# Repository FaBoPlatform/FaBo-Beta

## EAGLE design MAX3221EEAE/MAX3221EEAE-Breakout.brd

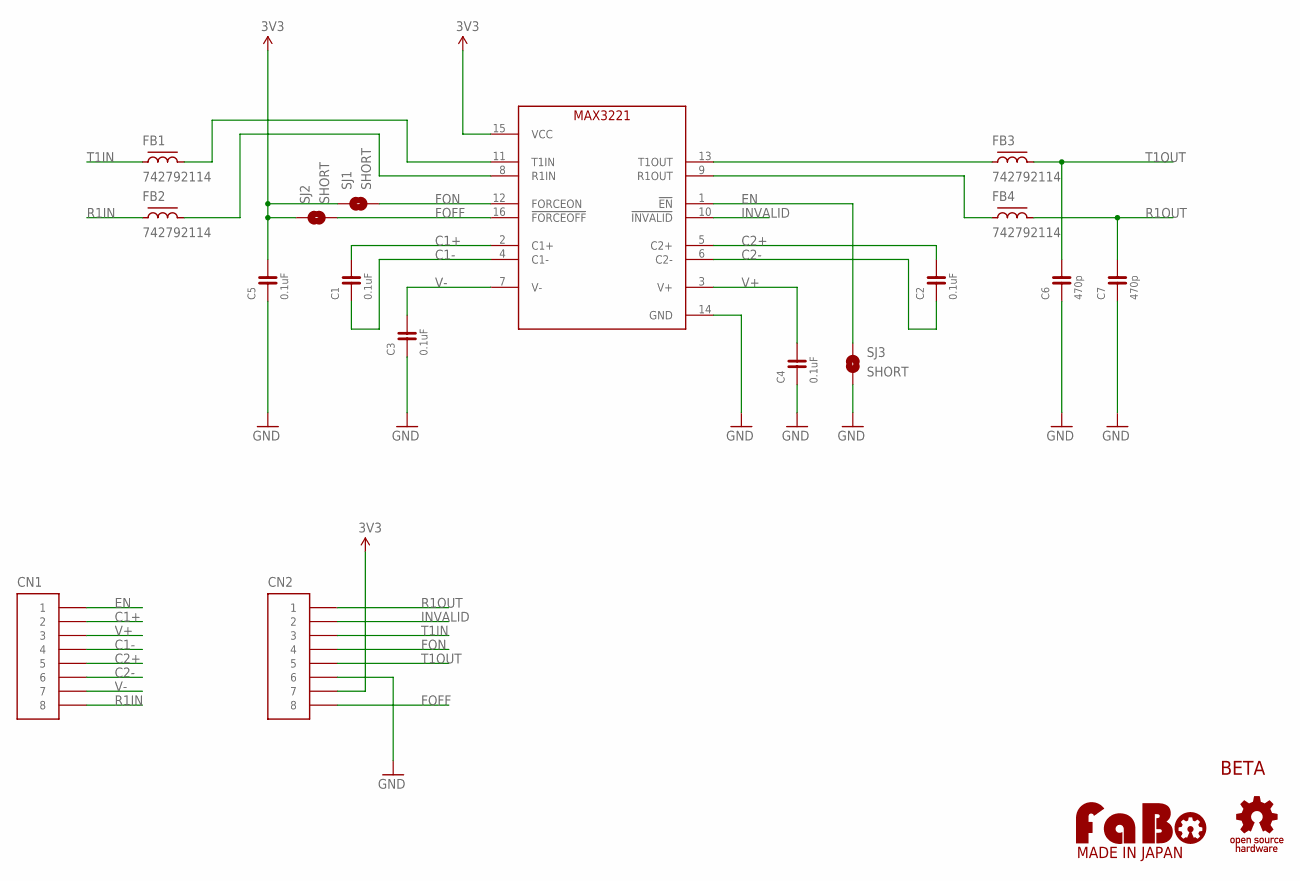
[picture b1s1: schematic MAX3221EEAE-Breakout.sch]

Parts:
C1, C2, C3, C4, C5: 0.1uF; 0603
C6, C7: 470p; 0603
CN1, CN2: PIN_HEADER_1X8; PIN_1X8
FB1, FB2, FB3, FB4: 742792114; EIA1206
IC1: MAX3221EEAE; SSOP-16
SJ1, SJ2, SJ3: SHORT; SMD-JUMPER-2-SHORT
U$2: LOGO_FABO-M_BOTTOM; LOGO_FABO_MS_BOTTOM
U$3: LOGO_OSHW-M_BOTTOM; LOGO_OSHW_M_BOTTOM

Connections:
3V3: C5.2, CN2.7, IC1.15 (VCC), SJ1.1, SJ2.1
C1+: C1.2, CN1.2, IC1.2 (C1+)
C1-: C1.1, CN1.4, IC1.4 (C1-)
C2+: C2.2, CN1.5, IC1.5 (C2+)
C2-: C2.1, CN1.6, IC1.6 (C2-)
EN: CN1.1, IC1.1 (!EN), SJ3.1
FOFF: CN2.8, IC1.16 (!FORCEOFF), SJ2.2
FON: CN2.4, IC1.12 (FORCEON), SJ1.2
GND: C3.1, C4.1, C5.1, C6.1, C7.1, CN2.6, IC1.14 (GND), SJ3.2
INVALID: CN2.2, IC1.10 (!INVALID)
R1IN: CN1.8, FB2.1
R1IN_R: FB2.2, IC1.8 (R1IN)
R1OUT: C7.2, CN2.1, FB4.2
R1OUT_R: FB4.1, IC1.9 (R1OUT)
T1IN: CN2.3, FB1.1
T1IN_R: FB1.2, IC1.11 (T1IN)
T1OUT: C6.2, CN2.5, FB3.2
T1OUT_R: FB3.1, IC1.13 (T1OUT)
V+: C4.2, CN1.3, IC1.3 (V+)
V-: C3.2, CN1.7, IC1.7 (V-)

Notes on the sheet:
BETA

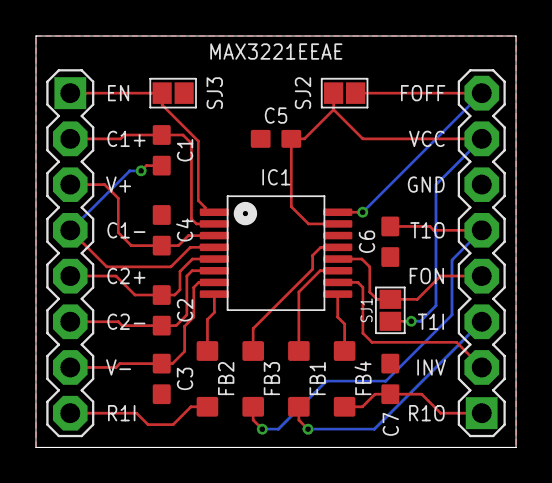
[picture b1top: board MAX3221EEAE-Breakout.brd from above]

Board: 2 copper layers, 26.7 x 22.9 mm, 19 parts (0 on the bottom side), 20 nets.

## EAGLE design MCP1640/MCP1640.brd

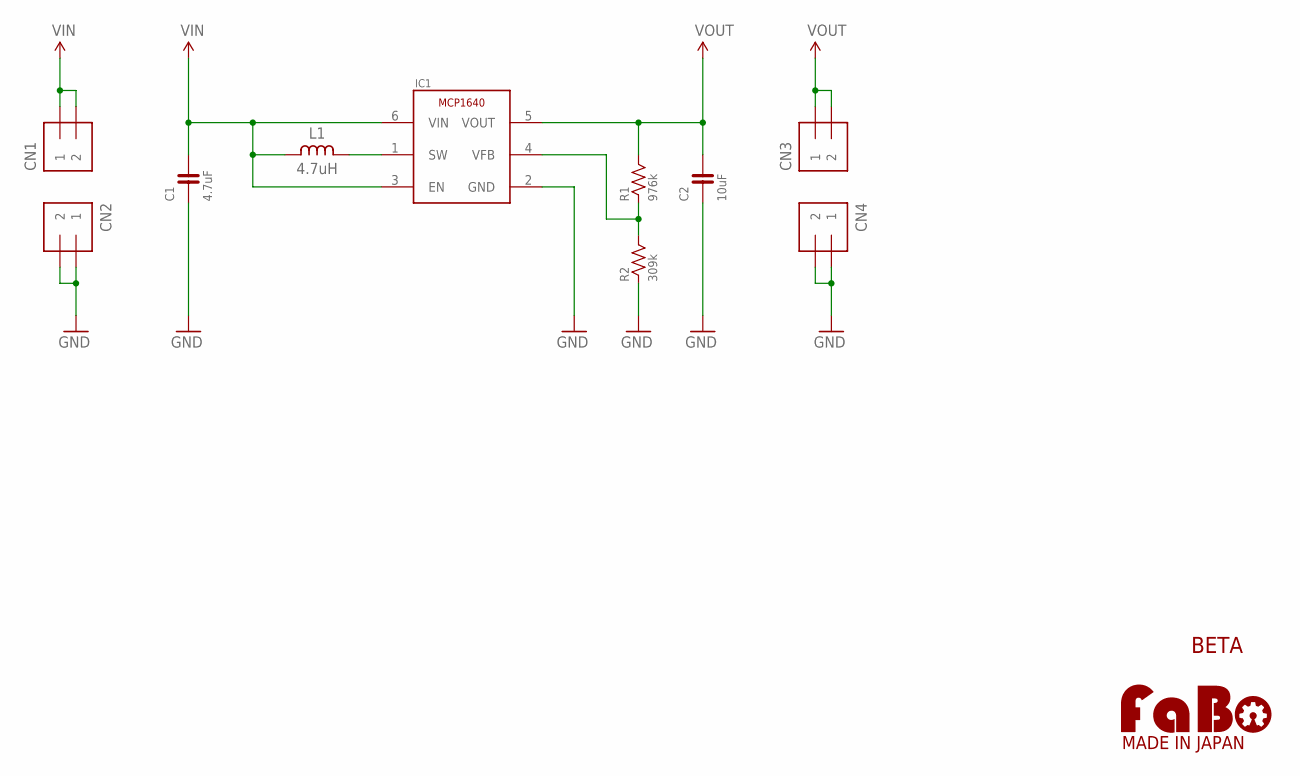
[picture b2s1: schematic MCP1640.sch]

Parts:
C1: 4.7uF; 0603-NARROW
C2: 10uF; 0603-NARROW
CN1, CN2, CN3, CN4: PIN_HEADER_1X2; PIN_1X2
IC1: MCP1640T; SOT-23-6
L1: 4.7uH; LQH3NPN
R1: 976k; 0603-NARROW
R2: 309k; 0603-NARROW
U$2: LOGO_FABO-M_BOTTOM; LOGO_FABO_MS_BOTTOM

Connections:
GND: C1.1, C2.1, CN2.1, CN2.2, CN4.1, CN4.2, IC1.2 (GND), R2.1
unnamed: IC1.1 (SW), L1.2
unnamed: IC1.4 (VFB), R1.1, R2.2
VIN: C1.2, CN1.1, CN1.2, IC1.3 (EN), IC1.6 (VIN), L1.1
VOUT: C2.2, CN3.1, CN3.2, IC1.5 (VOUT), R1.2

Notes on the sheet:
BETA

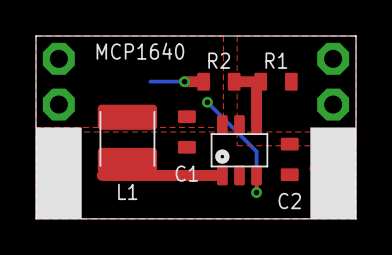
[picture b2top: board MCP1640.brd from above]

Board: 2 copper layers, 17.8 x 10.2 mm, 11 parts (0 on the bottom side), 5 nets.

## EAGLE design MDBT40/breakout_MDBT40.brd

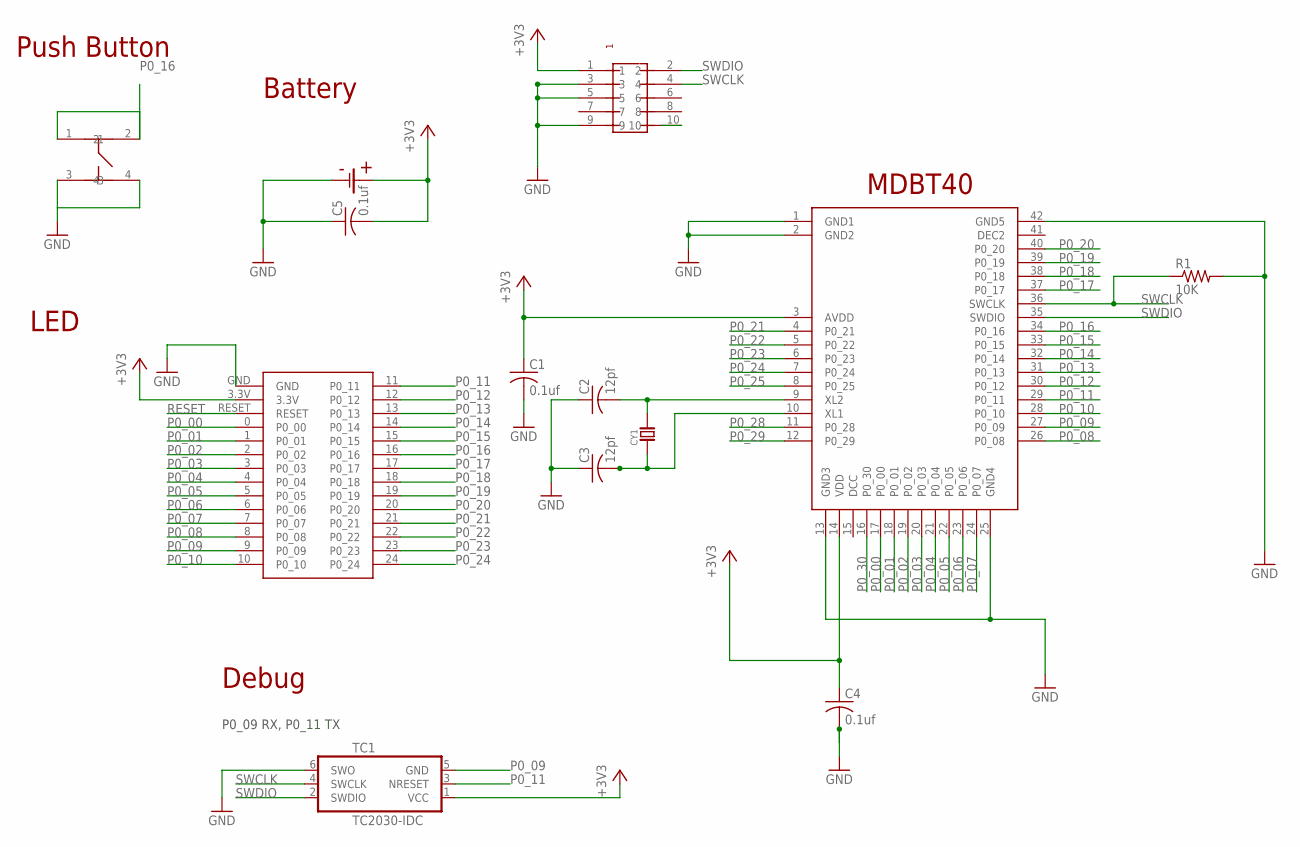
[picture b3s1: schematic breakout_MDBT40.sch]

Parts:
C1, C4, C5: 0.1uf; C0603
C2, C3: 12pf; C0603
CY1: CRYSTALABS07; ABRACOM-ABS07-32.768KHZ
R1: 10K; R0603
TC1: TC2030-IDC
U$1: RAYTAC-MDBT40
U$3: BLE-BREAKOUT-NORDIC
U$4: PIN-HEADER-SMT(1.27MM)2X5
U$5: SWICTH-4P(KMR2); SWITCH-4P(KMR2)
U$8: SMTU-TOP2032; SMTU-2032

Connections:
+3V3: C1.1, C4.1, C5.2, TC1.1 (VCC), U$1.3 (AVDD), U$1.14 (VDD), U$3.3.3V, U$4.1, U$8.+
GND: C1.2, C2.1, C3.1, C4.2, C5.1, R1.2, TC1.6 (SWO), U$1.1 (GND1), U$1.2 (GND2), U$1.13 (GND3), U$1.25 (GND4), U$1.42 (GND5), U$3.GND, U$4.3, U$4.5, U$4.9, U$5.3, U$5.4, U$8.-
unnamed: C2.2, CY1.P$2, U$1.9 (XL2)
unnamed: C3.2, CY1.P$1, U$1.10 (XL1)
P0_00: U$1.17 (P0_00), U$3.0 (P0_00)
P0_01: U$1.18 (P0_01), U$3.1 (P0_01)
P0_02: U$1.19 (P0_02), U$3.2 (P0_02)
P0_03: U$1.20 (P0_03), U$3.3 (P0_03)
P0_04: U$1.21 (P0_04), U$3.4 (P0_04)
P0_05: U$1.22 (P0_05), U$3.5 (P0_05)
P0_06: U$1.23 (P0_06), U$3.6 (P0_06)
P0_07: U$1.24 (P0_07), U$3.7 (P0_07)
P0_08: U$1.26 (P0_08), U$3.8 (P0_08)
P0_09: TC1.5 (GND), U$1.27 (P0_09), U$3.9 (P0_09)
P0_10: U$1.28 (P0_10), U$3.10 (P0_10)
P0_11: TC1.3 (NRESET), U$1.29 (P0_11), U$3.11 (P0_11)
P0_12: U$1.30 (P0_12), U$3.12 (P0_12)
P0_13: U$1.31 (P0_13), U$3.13 (P0_13)
P0_14: U$1.32 (P0_14), U$3.14 (P0_14)
P0_15: U$1.33 (P0_15), U$3.15 (P0_15)
P0_16: U$1.34 (P0_16), U$3.16 (P0_16), U$5.1, U$5.2
P0_17: U$1.37 (P0_17), U$3.17 (P0_17)
P0_18: U$1.38 (P0_18), U$3.18 (P0_18)
P0_19: U$1.39 (P0_19), U$3.19 (P0_19)
P0_20: U$1.40 (P0_20), U$3.20 (P0_20)
P0_21: U$1.4 (P0_21), U$3.21 (P0_21)
P0_22: U$1.5 (P0_22), U$3.22 (P0_22)
P0_23: U$1.6 (P0_23), U$3.23 (P0_23)
P0_24: U$1.7 (P0_24), U$3.24 (P0_24)
P0_25: U$1.8 (P0_25)
P0_28: U$1.11 (P0_28)
P0_29: U$1.12 (P0_29)
P0_30: U$1.16 (P0_30)
RESET: U$3.RESET
RESET1: U$4.10
SWCLK: R1.1, TC1.4 (SWCLK), U$1.36 (SWCLK), U$4.4
SWDIO: TC1.2 (SWDIO), U$1.35 (SWDIO), U$4.2

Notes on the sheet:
Battery
Push Button
MDBT40
LED
Debug
P0_09 RX, P0_11 TX

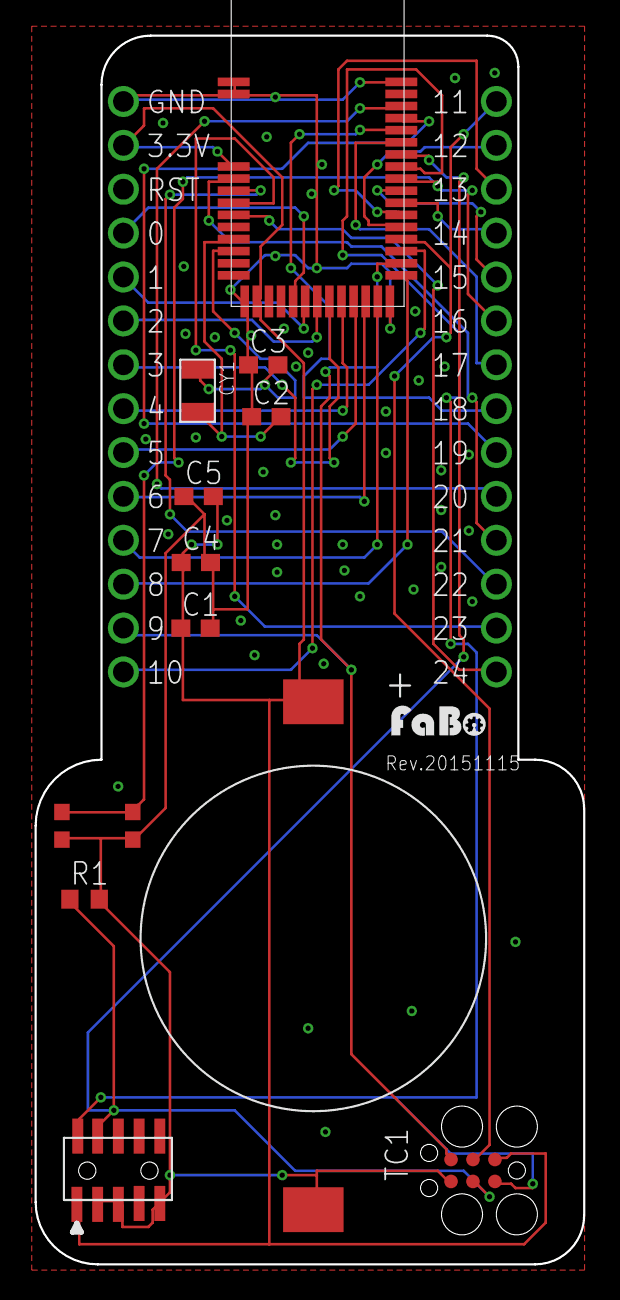
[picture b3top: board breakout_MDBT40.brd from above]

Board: 2 copper layers, 31.8 x 71.1 mm, 14 parts (0 on the bottom side), 31 nets.

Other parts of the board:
U$7: LOGO_FABO_S

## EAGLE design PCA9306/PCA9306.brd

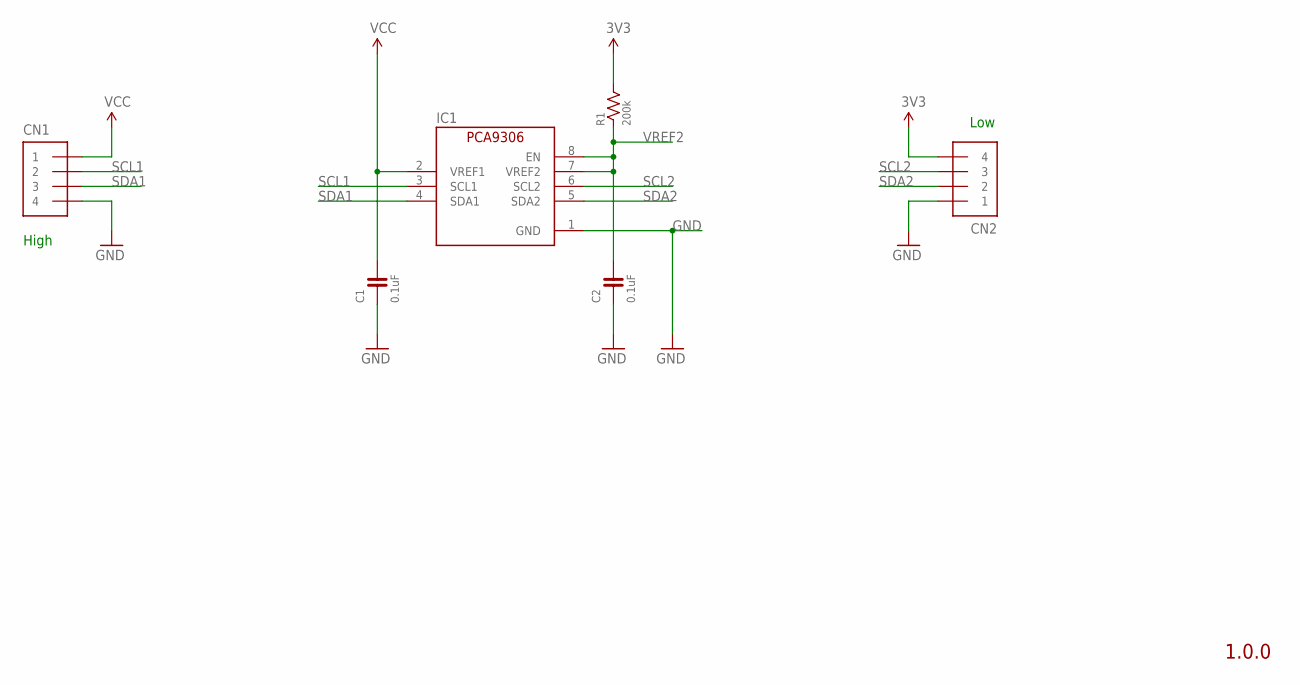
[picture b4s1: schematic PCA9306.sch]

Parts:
C1, C2: 0.1uF; 0603
CN1, CN2: PIN_HEADER_1X4; PIN_1X4_SNEAKY
IC1: TI-PCA9306DQE; TI-PCA9306
R1: 200k; 0603

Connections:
3V3: CN2.4, R1.2
GND: C1.1, C2.1, CN1.4, CN2.1, IC1.1 (GND)
SCL1: CN1.2, IC1.3 (SCL1)
SCL2: CN2.3, IC1.6 (SCL2)
SDA1: CN1.3, IC1.4 (SDA1)
SDA2: CN2.2, IC1.5 (SDA2)
VCC: C1.2, CN1.1, IC1.2 (VREF1)
VREF2: C2.2, IC1.7 (VREF2), IC1.8 (EN), R1.1

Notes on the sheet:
1.0.0
High
Low

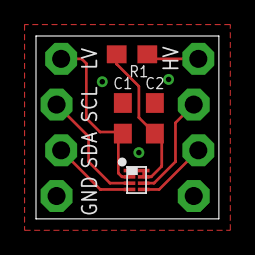
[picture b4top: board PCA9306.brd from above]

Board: 2 copper layers, 10.2 x 10.2 mm, 6 parts (0 on the bottom side), 8 nets.

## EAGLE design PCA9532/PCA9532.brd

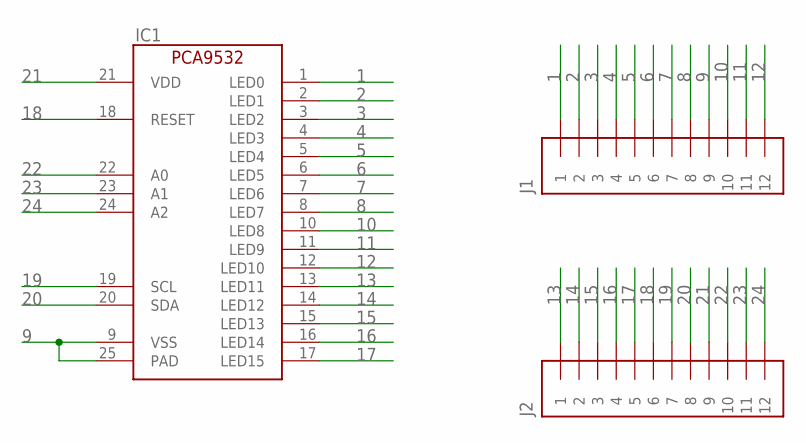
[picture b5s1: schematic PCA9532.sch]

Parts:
IC1: PCA9532BS; HVQFN24
J1, J2: PIN_HEADER_1X12; PIN_1X12_SNEAKY

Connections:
1: IC1.1 (LED0), J1.1
2: IC1.2 (LED1), J1.2
3: IC1.3 (LED2), J1.3
4: IC1.4 (LED3), J1.4
5: IC1.5 (LED4), J1.5
6: IC1.6 (LED5), J1.6
7: IC1.7 (LED6), J1.7
8: IC1.8 (LED7), J1.8
9: IC1.9 (VSS), IC1.25 (PAD), J1.9
10: IC1.10 (LED8), J1.10
11: IC1.11 (LED9), J1.11
12: IC1.12 (LED10), J1.12
13: IC1.13 (LED11), J2.1
14: IC1.14 (LED12), J2.2
15: IC1.15 (LED13), J2.3
16: IC1.16 (LED14), J2.4
17: IC1.17 (LED15), J2.5
18: IC1.18 (RESET), J2.6
19: IC1.19 (SCL), J2.7
20: IC1.20 (SDA), J2.8
21: IC1.21 (VDD), J2.9
22: IC1.22 (A0), J2.10
23: IC1.23 (A1), J2.11
24: IC1.24 (A2), J2.12

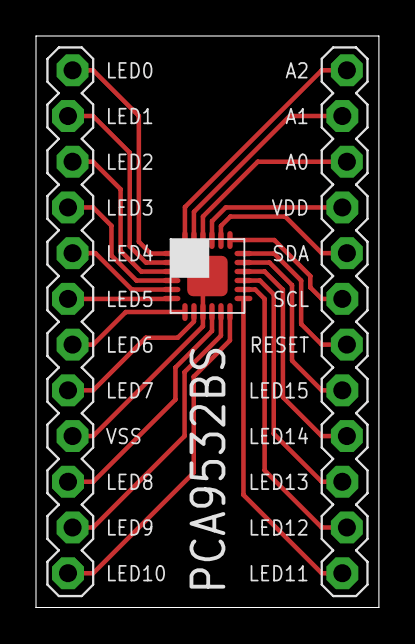
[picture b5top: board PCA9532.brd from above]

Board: 2 copper layers, 19.1 x 31.8 mm, 3 parts (0 on the bottom side), 24 nets.

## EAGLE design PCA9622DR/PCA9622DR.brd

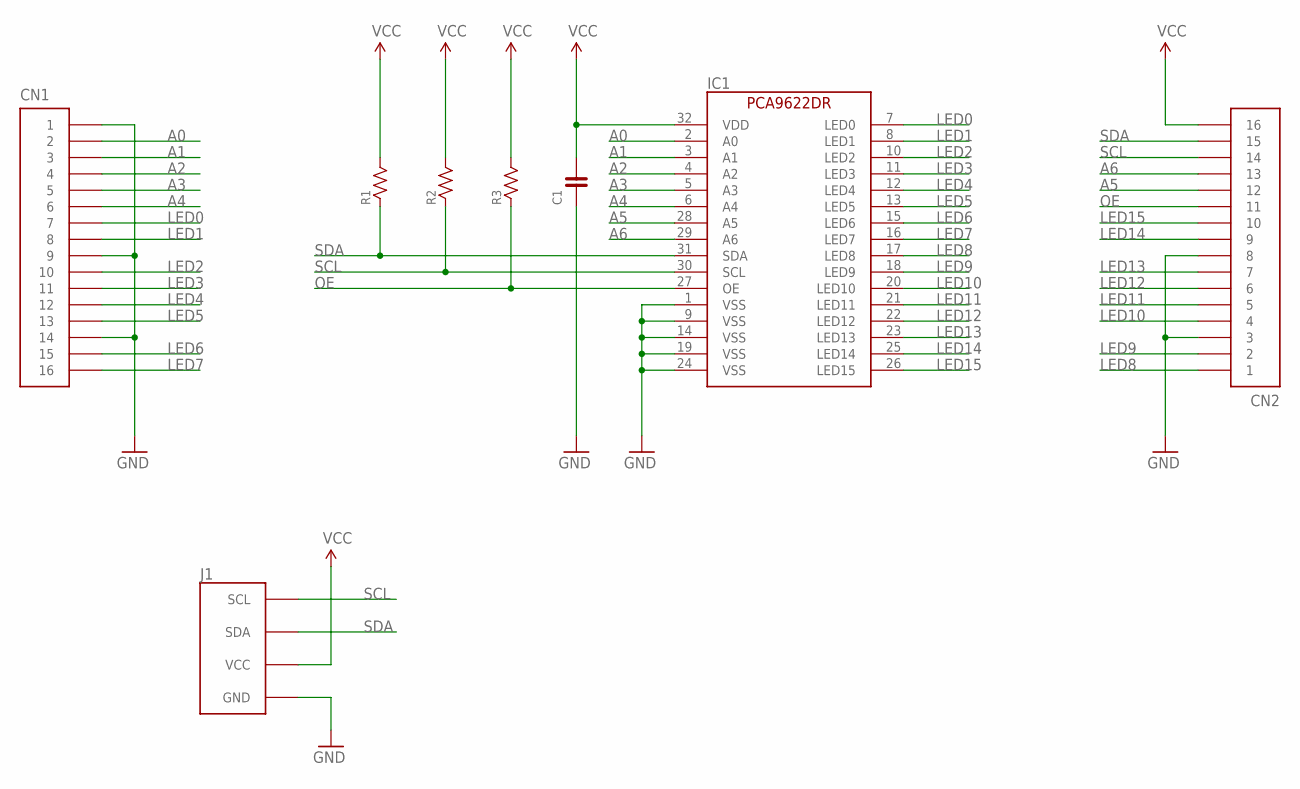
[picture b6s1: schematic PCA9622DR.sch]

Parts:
C1: CAPACITOR-0603; 0603
CN1, CN2: PIN_HEADER_1X16; PIN_1X16_SNEAKY
IC1: PCA9622DR; TSSOP32
J1: FABO_BRICK_I2C-CONNECTOR; FABO_BRICK_I2C_CONNECTOR
R1, R2, R3: RESISTOR-0603; 0603

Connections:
A0: CN1.2, IC1.2 (A0)
A1: CN1.3, IC1.3 (A1)
A2: CN1.4, IC1.4 (A2)
A3: CN1.5, IC1.5 (A3)
A4: CN1.6, IC1.6 (A4)
A5: CN2.12, IC1.28 (A5)
A6: CN2.13, IC1.29 (A6)
GND: C1.1, CN1.1, CN1.9, CN1.14, CN2.3, CN2.8, IC1.1 (VSS), IC1.9 (VSS), IC1.14 (VSS), IC1.19 (VSS), IC1.24 (VSS), J1.GND
LED0: CN1.7, IC1.7 (LED0)
LED1: CN1.8, IC1.8 (LED1)
LED2: CN1.10, IC1.10 (LED2)
LED3: CN1.11, IC1.11 (LED3)
LED4: CN1.12, IC1.12 (LED4)
LED5: CN1.13, IC1.13 (LED5)
LED6: CN1.15, IC1.15 (LED6)
LED7: CN1.16, IC1.16 (LED7)
LED8: CN2.1, IC1.17 (LED8)
LED9: CN2.2, IC1.18 (LED9)
LED10: CN2.4, IC1.20 (LED10)
LED11: CN2.5, IC1.21 (LED11)
LED12: CN2.6, IC1.22 (LED12)
LED13: CN2.7, IC1.23 (LED13)
LED14: CN2.9, IC1.25 (LED14)
LED15: CN2.10, IC1.26 (LED15)
OE: CN2.11, IC1.27 (OE), R3.1
SCL: CN2.14, IC1.30 (SCL), J1.SCL, R2.1
SDA: CN2.15, IC1.31 (SDA), J1.SDA, R1.1
VCC: C1.2, CN2.16, IC1.32 (VDD), J1.VCC, R1.2, R2.2, R3.2

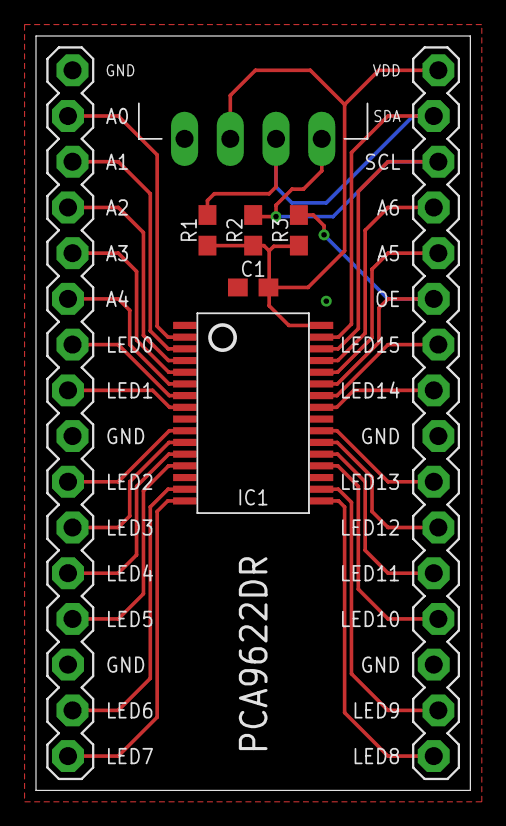
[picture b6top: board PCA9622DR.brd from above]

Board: 2 copper layers, 24.1 x 41.9 mm, 8 parts (0 on the bottom side), 28 nets.

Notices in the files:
parts and their libraries:
FaBo-Capacitor: Released under the Creative Commons Attribution-ShareAlike 4.0 License
https://creativecommons.org/licenses/by-sa/4.0
FaBo-etc: Released under the Creative Commons
SparkFun: Licensing: CC v3.0 Share-Alike You are welcome to use this library for commercial purposes.
